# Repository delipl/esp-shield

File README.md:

# esp-shield
Shield for Arduino Uno to upload and communicate with ESP-01 and ESP-12E.
# Features
- programmable ESP
- soft serial for arduino
- jumper between RX TX frmm Arduino and ESP for programming mode and communication
- extruded ESP-12E pinout

# 3D model photos

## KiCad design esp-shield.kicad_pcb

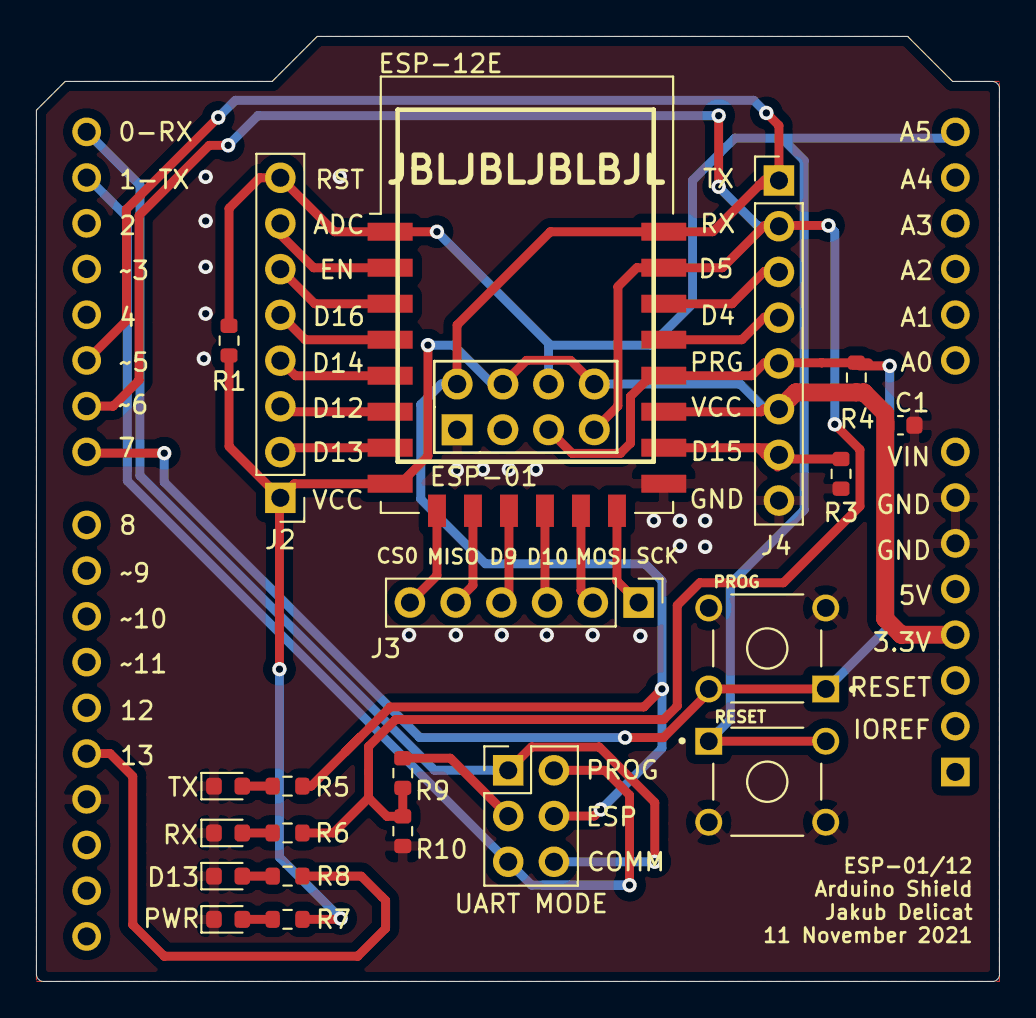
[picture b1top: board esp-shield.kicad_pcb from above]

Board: 2 copper layers, 53.5 x 52.5 mm, 23 parts (1 on the bottom side), 29 nets.

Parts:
A1: Arduino_UNO_R3
BUILTIN1: D13; LED_0603_1608Metric
C1: C; C_0603_1608Metric
D1: TX; LED_0603_1608Metric
ESP-12E1: ESP-12E
J1: UART MODE; PinHeader_2x03_P2.54mm_Vertical
J2, J4: Conn_01x08; PinHeader_1x08_P2.54mm_Vertical
J3: Conn_01x06; PinHeader_1x06_P2.54mm_Vertical
PWR1: PWR; LED_0603_1608Metric
R1, R3, R4: 10kOhm; R_0603_1608Metric
R5, R6, R7, R8: R; R_0603_1608Metric
R9: 1kOhm; R_0603_1608Metric
R10: 2k2OHM; R_0603_1608Metric
RX1: RX; LED_0603_1608Metric
SW1: RESET; TE_1-1825910-4
SW2: PROG; TE_1-1825910-4
U2: ESP-01

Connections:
/RX_AR: A1.15, J1.1, J1.6
/TX_AR: A1.16, J1.2, J1.5
ADC: ESP-12E1.2, J2.7
CS0: ESP-12E1.9, J3.6
D13: A1.28, R8.1
EN: ESP-12E1.3, J2.6
GND: A1.6, A1.7, A1.29, BUILTIN1.1, C1.2, D1.1, ESP-12E1.15, J4.8, PWR1.1, R3.2, R10.1, RX1.1, SW1.3, SW1.4, SW2.3, SW2.4, U2.1
GPIO4: ESP-12E1.19, J4.4
GPIO5: ESP-12E1.20, J4.3
GPIO9: ESP-12E1.11, J3.4
GPIO10: ESP-12E1.12, J3.3
GPIO12: ESP-12E1.6, J2.3
GPIO13: ESP-12E1.7, J2.2
GPIO14: ESP-12E1.5, J2.4
GPIO15: ESP-12E1.16, J4.7, R3.1
GPIO16: ESP-12E1.4, J2.5
MISO: ESP-12E1.10, J3.5
MOSI: ESP-12E1.13, J3.2
unnamed: BUILTIN1.2, R8.2
unnamed: D1.2, R5.2
unnamed: PWR1.2, R7.2
unnamed: R6.2, RX1.2
PROG: A1.22, ESP-12E1.18, J4.5, R4.2, SW2.1, SW2.2, U2.3
RST: A1.14, ESP-12E1.1, J2.8, R1.2, SW1.1, SW1.2, U2.7
RX_PROG: A1.21, ESP-12E1.21, J4.2, R6.1, R9.1, R10.2, U2.4
RX_PROG5V: J1.3, R9.2
SCLK: ESP-12E1.14, J3.1
TX_PROG: A1.20, ESP-12E1.22, J1.4, J4.1, R5.1, U2.5
VCC: A1.4, C1.1, ESP-12E1.8, ESP-12E1.17, J2.1, J4.6, R1.1, R4.1, R7.1, U2.6, U2.8

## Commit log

2021-11-19 Project ready for order
2021-11-19 Added photos
2021-11-19 Push unsaved things
2021-11-20 Added esp112E labeling
2021-11-21 Added Arduino pinout labels
2021-11-21 FLipped arduino xD
2021-11-21 ADDED JP ASD
